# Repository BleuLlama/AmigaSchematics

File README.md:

# AmigaSchematics
Schematics of various Commodore Amiga related items

# Overview

This project contains some schematics that I've reproduced from
various sources that are otherwise not available. They have been
made using KiCad 4.0.7 on my Mac, although they should load in KiCad
4 on any platform.

The projects included here are:

* A500_kyb_Mitsumi - Amiga 500 keyboard with Mitsumi board. (common)

* Controllers/CD32 - CD32 wired controller (with Red/Yellow/Green/Blue buttons)

Soon perhaps:
* A500_kyb_2Conn - Early Amiga 500 keyboard with two ribbon connectors to the scan matrix

# Note

I'm pretty green with respect to KiCad, so if there are any things 
in here that I did poorly or in a weird way, that's probably the 
reason. I am always open to comments and suggestions for improving
my abilities, so please feel free to contribute constructive 
criticism.  :)

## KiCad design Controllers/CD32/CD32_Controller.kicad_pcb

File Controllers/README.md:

# Controllers

This directory contains schematics captured for various controllers 
that are plugged in through the DB9 "joystick" port on the Amiga.

Included here are:

* [CD32] four-button controller for the Amiga CD32.

* [Jaguar] jaguar controller.

I know it's not Amiga related, but i wanted to put it online somewhere.

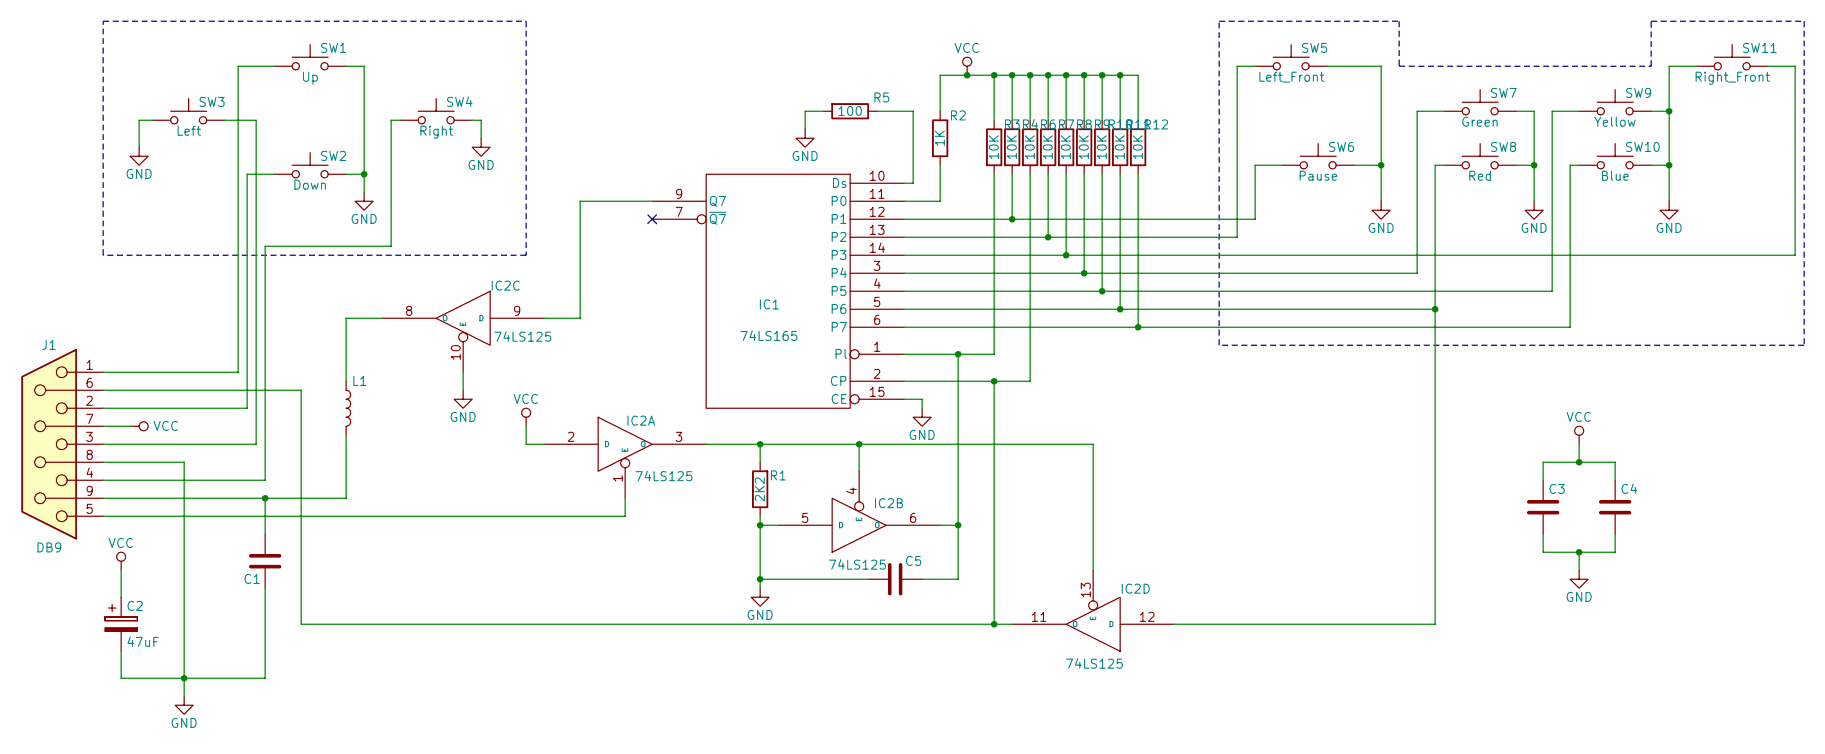
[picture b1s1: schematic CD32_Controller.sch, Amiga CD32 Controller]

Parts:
C1: 220uF; CP_Radial_D6.3mm_P2.50mm
C2: 47uF; CP_Radial_D6.3mm_P2.50mm
C3, C4: 100n; C_Axial_L5.1mm_D3.1mm_P7.50mm_Horizontal
C5: C; C_Axial_L5.1mm_D3.1mm_P7.50mm_Horizontal
IC1: 74LS165; DIP-16_W7.62mm_LongPads
IC2: 74LS125; DIP-14_W7.62mm_LongPads
J1: DB9; DSUB-9_Male_Horizontal_P2.77x2.84mm_EdgePinOffset4.94mm_Hou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
L1: L; L_Axial_L5.3mm_D2.2mm_P10.16mm_Horizontal_Vishay_IM-1
R1: 2K2; R_Axial_DIN0207_L6.3mm_D2.5mm_P10.16mm_Horizontal
R2: 1K; R_Axial_DIN0207_L6.3mm_D2.5mm_P10.16mm_Horizontal
R3, R4, R6, R7, R8, R9, R10, R11, R12: 10K; R_Axial_DIN0207_L6.3mm_D2.5mm_P10.16mm_Horizontal
R5: 100; R_Axial_DIN0207_L6.3mm_D2.5mm_P10.16mm_Horizontal
SW1: Up; SW_PUSH_6mm_h4.3mm
SW2: Down; SW_PUSH_6mm_h4.3mm
SW3: Left; SW_PUSH_6mm_h4.3mm
SW4: Right; SW_PUSH_6mm_h4.3mm
SW5: Left_Front; SW_PUSH_6mm_h4.3mm
SW6: Pause; SW_PUSH_6mm_h4.3mm
SW7: Green; SW_PUSH_6mm_h4.3mm
SW8: Red; SW_PUSH_6mm_h4.3mm
SW9: Yellow; SW_PUSH_6mm_h4.3mm
SW10: Blue; SW_PUSH_6mm_h4.3mm
SW11: Right_Front; SW_PUSH_6mm_h4.3mm

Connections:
GND: C1.2, C2.2, C3.2, C4.2, C5.2, IC1.8 (GND), IC1.15 (CE), IC2.5 (D), IC2.7 (GND), IC2.10 (E), J1.8, R1.1, R5.2, SW1.2, SW2.2, SW3.1, SW4.2, SW5.2, SW6.2, SW7.2, SW8.2, SW9.2, SW10.2, SW11.1
unnamed: C1.1, J1.9, L1.2
unnamed: C5.1, IC1.1 (Pl), IC2.6 (O), R3.2
unnamed: IC1.2 (CP), IC2.11 (O), J1.6, R6.2
unnamed: IC1.3 (P4), R9.2, SW7.1
unnamed: IC1.4 (P5), R10.2, SW9.1
unnamed: IC1.5 (P6), IC2.12 (D), R11.2, SW8.1
unnamed: IC1.6 (P7), R12.2, SW10.1
unnamed: IC1.9 (Q7), IC2.9 (D)
unnamed: IC1.10 (Ds), R5.1
unnamed: IC1.11 (P0), R2.2
unnamed: IC1.12 (P1), R4.2, SW6.1
unnamed: IC1.13 (P2), R7.2, SW5.1
unnamed: IC1.14 (P3), R8.2, SW11.2
unnamed: IC2.1 (E), J1.5
unnamed: IC2.8 (O), L1.1
unnamed: IC2.3 (O), IC2.4 (E), IC2.13 (E), R1.2
unnamed: J1.1, SW1.1
unnamed: J1.2, SW2.1
unnamed: J1.3, SW3.2
unnamed: J1.4, SW4.1
VCC: C2.1, C3.1, C4.1, IC1.16 (VCC), IC2.2 (D), IC2.14 (VCC), J1.7, R2.1, R3.1, R4.1, R6.1, R7.1, R8.1, R9.1, R10.1, R11.1, R12.1

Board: 2 copper layers, 33 parts (0 on the bottom side), 22 nets, no tracks yet.

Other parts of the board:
RA1: 10K; R_Array_SIP10

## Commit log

2018-02-11 Initial checkin
2018-02-11 Corrections
2018-02-11 Removed temp files
2018-03-09 Added CD32 controller
2018-03-09 Readme
2020-04-12 Kicad 5 conversion (automatic upon schematic opening): - No changes aside from the conversion were made to the files. - Added project conversion report. - Added .gitignore to avoid versioning unneces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
2020-04-12 Miscellaneous small reworks: - Renamed symbols to conform to those of the official Commodore A500/A500+ schematics. - Fixed Labels to properly match their Input/Output status (they were showing as bi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
2020-04-12 MOS 6570 pins fixes, renames, spacing and additional labelling. - MOS 6570: - Renamed pins to not include their in-circuit function but just their name as specified by MOS. Labels were moved to wire/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
2023-10-16 Added Atari Jaguar controller
